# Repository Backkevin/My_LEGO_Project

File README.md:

# My_LEGO_Project

based on MattzoController Firmware V0.3

 My Lego boards with PCF8574 ,MC23017 ,PCA9685 ,L9110
 
 https://www.pcbway.com/setinvite.aspx?inviteid=295257
 
 -----------------------------------------------------------------
 
 BUS PINOUT from CPU Board to other Boards
+ PIN 1 ---> D0
+ PIN 2 ---> SCL (D1)
+ PIN 3 ---> SDA (D2)
+ PIN 4 ---> D3
+ PIN 5 ---> D4
+ PIN 6 ---> D5
+ PIN 7 ---> D6
+ PIN 8 ---> D7
+ PIN 9 ---> D8
+ PIN 10 --> RX
+ PIN 11 --> TX
+ PIN 12 --> D9
+ PIN 13 --> +5VDC (Bug 3A/5A /\ AC/DC BUG 1A)   Layouts are not ready for the 5A BUG (this bug is bigger, change in the next layout)
+ PIN 14 --> +5VDC (Bug 3A/5A /\ AC/DC BUG 1A)   Layouts are not ready for the 5A BUG (this bug is bigger, change in the next layout)
+ PIN 15 --> GND
+ PIN 16 --> GND

-----------------------------------------------------------------

+ PCF8574 adresse
>
+ MCP23017 adresse
>
+ PCA9685 adresse
>
-----------------------------------------------------------------

+ Conpatible sensors and actors
>
>
>
>
>
>
>
>
-----------------------------------------------------------------
-----------------------------------------------------------------

+ [MattzoController_Sensor_Digital_I2C](https://github.com/Backkevin/My_LEGO_Project/tree/master/MattzoController_Sensor_Digital_I2C)

	+ V2.1
		* Work 90%
		* Partlist KO
		* [INO FILE](https://github.com/Backkevin/My_LEGO_Project/tree/master/MattzoController_Sensor_Digital_I2C/INO/MattzoController_Sensor_Digital_I2C)
		* [GERBER FILES](https://github.com/Backkevin/My_LEGO_Project/tree/master/MattzoController_Sensor_Digital_I2C/GERBER%20FILES)
		* [EAGLE FILES](https://github.com/Backkevin/My_LEGO_Project/tree/master/MattzoController_Sensor_Digital_I2C/EAGLE)
		* [PDF FILES](https://github.com/Backkevin/My_LEGO_Project/tree/master/MattzoController_Sensor_Digital_I2C/PDF)
		
	+ Work in progress !
>+ CPU V3.0
>
>+ INPUT V2.1
>
-----------------------------------------------------------------

+ [MattzoController_Signal_I2C](https://github.com/Backkevin/My_LEGO_Project/tree/master/MattzoController_Signal_I2C)

	+ V2.1
		* Work 100%
		* Partlist KO
		* [INO FILE](https://github.com/Backkevin/My_LEGO_Project/tree/master/MattzoController_Signal_I2C/INO/MattzoController_Signal_I2C)
		* [GERBER FILES](https://github.com/Backkevin/My_LEGO_Project/tree/master/MattzoController_Signal_I2C/GERBER%20FILES)
		* [EAGLE FILES](https://github.com/Backkevin/My_LEGO_Project/tree/master/MattzoController_Signal_I2C/EAGLE)
		* [PDF FILES](https://github.com/Backkevin/My_LEGO_Project/tree/master/MattzoController_Signal_I2C/PDF)
		
>+ CPU V3.0
>
>+ OUTPUT V2.1
>
>+ Tower
>
-----------------------------------------------------------------

+ [MattzoController_Switch_I2C](https://github.com/Backkevin/My_LEGO_Project/tree/master/MattzoController_Switch_I2C)

	+ V2.0
		* Work 90%
		* Partlist KO
		* [INO FILE](https://github.com/Backkevin/My_LEGO_Project/tree/master/MattzoController_Switch_I2C/INO/MattzoController_Switch_I2C)
		* [GERBER FILES](https://github.com/Backkevin/My_LEGO_Project/tree/master/MattzoController_Switch_I2C/GERBER%20FILES)
		* [EAGLE FILES](https://github.com/Backkevin/My_LEGO_Project/tree/master/MattzoController_Switch_I2C/EAGLE)
		* [PDF FILES](https://github.com/Backkevin/My_LEGO_Project/tree/master/MattzoController_Switch_I2C/PDF)
		
	+ Work in progress !
>+ CPU V3.0
>
>+ PWM V2.0
>
-----------------------------------------------------------------

+ [MattzoStationController_I2C](https://github.com/Backkevin/My_LEGO_Project/tree/master/MattzoStationController_I2C)

	+ V2.0
		* Work 90%
		* Partlist KO
		* [INO FILE](https://github.com/Backkevin/My_LEGO_Project/tree/master/MattzoStationController_I2C/INO/MattzoStationController_I2C)
		* [GERBER FILES](https://github.com/Backkevin/My_LEGO_Project/tree/master/MattzoStationController_I2C/GERBER%20FILES)
		* [EAGLE FILES](https://github.com/Backkevin/My_LEGO_Project/tree/master/MattzoStationController_I2C/EAGLE)
		* [PDF FILES](https://github.com/Backkevin/My_LEGO_Project/tree/master/MattzoStationController_I2C/PDF)
		
	+ Work in progress !
>+ CPU V3.0
>
>+ INPUT V2.1
>
>+ OUTPUT V2.1
>
>+ PWM V2.0
>
>+ Tower
>
-----------------------------------------------------------------

-----------------------------------------------------------------

+ [MCP23017 Boards I16](https://github.com/Backkevin/My_LEGO_Project/tree/master/MCP23017%20Boards/I16)

	+ V1.0
		* Work 50%
		* Partlist KO
		* [GERBER FILES](https://github.com/Backkevin/My_LEGO_Project/tree/master/MCP23017%20Boards/I16/GERBER%20FILES)
		* [EAGLE FILES](https://github.com/Backkevin/My_LEGO_Project/tree/master/MCP23017%20Boards/I16/EAGLE)
		* [PDF FILES](https://github.com/Backkevin/My_LEGO_Project/tree/master/MCP23017%20Boards/I16/PDF)
		
	+ Work in progress !
>+ CPU V3.0
>
>+ I16 V1.0
>
-----------------------------------------------------------------

+ [MCP23017 Boards O8](https://github.com/Backkevin/My_LEGO_Project/tree/master/MCP23017%20Boards/O8)

+ !!!!!!!  max I for the MCP23017 125ma  so we need to change the R470 resistors to 1K2 
+ or
+ dont install the control LEDs on the board so you can keep the R470 resistors

	+ V1.0
		* Work 50%
		* Partlist KO
		* [GERBER FILES](https://github.com/Backkevin/My_LEGO_Project/tree/master/MCP23017%20Boards/O8/GERBER%20FILES)
		* [EAGLE FILES](https://github.com/Backkevin/My_LEGO_Project/tree/master/MCP23017%20Boards/O8/EAGLE)
		* [PDF FILES](https://github.com/Backkevin/My_LEGO_Project/tree/master/MCP23017%20Boards/O8/PDF)
		
	+ Work in progress !
>+ CPU V3.0
>
>+ O8 V1.0
>
-----------------------------------------------------------------

+ [MCP23017 Boards I8O4](https://github.com/Backkevin/My_LEGO_Project/tree/master/MCP23017%20Boards/I8O4)

	+ V1.0
		* Work 50%
		* Partlist KO
		* [GERBER FILES](https://github.com/Backkevin/My_LEGO_Project/tree/master/MCP23017%20Boards/I8O4/GERBER%20FILES)
		* [EAGLE FILES](https://github.com/Backkevin/My_LEGO_Project/tree/master/MCP23017%20Boards/I8O4/EAGLE)
		* [PDF FILES](https://github.com/Backkevin/My_LEGO_Project/tree/master/MCP23017%20Boards/I8O4/PDF)
		
	+ Work in progress !
>+ V3.0
>
>+ V1.0
>
-----------------------------------------------------------------

-----------------------------------------------------------------

+ [L9110 Board](https://github.com/Backkevin/My_LEGO_Project/tree/master/L9110%20Board)

	+ V1.0
		* Work 25%
		* Partlist KO
		* [GERBER FILES](https://github.com/Backkevin/My_LEGO_Project/tree/master/L9110%20Board/GERBER%20FILES)
		* [EAGLE FILES](https://github.com/Backkevin/My_LEGO_Project/tree/master/L9110%20Board/EAGLE)
		* [PDF FILES](https://github.com/Backkevin/My_LEGO_Project/tree/master/L9110%20Board/PDF)
		
	+ Work in progress !
>+ CPU V3.0
>
>+ L9110 V1.0
>
-----------------------------------------------------------------

SENSOR BOARDS
 
-----------------------------------------------------------------
Experimental
-----------------------------------------------------------------

+ Sensor_GP1A57HRJ00F_board_V_1_0
>
-----------------------------------------------------------------
Sensor_TCRT5000_board_V_1_0
>
-----------------------------------------------------------------
+ Sensor_board_V_1_0
>
-----------------------------------------------------------------
+ Sensor_board_2_V_1_0
>
-----------------------------------------------------------------
+ Sensor_laser_board_V_1_0
>
-----------------------------------------------------------------

-----------------------------------------------------------------
-----------------------------------------------------------------
>i work on a new software based on MattzoController Firmware V0.41

+ [FULL BRIDGE](https://github.com/Backkevin/My_LEGO_Project/tree/master/Universal%20Driver/FULL%20BRIDGE)     
	* --> for 2 x L9110 Board + 2 x I8O4 Board  
	* --> 4 motors, 8 signals, 24 inputs
	* --> AUTO MODE
	* --> later           
+ [FULL CROSSING](https://github.com/Backkevin/My_LEGO_Project/tree/master/Universal%20Driver/FULL%20CROSSING)  
	* --> for PCA9685 Board + 2 x I8O4 Board + 2 x O8 Board                             
	* --> 32 PWMs, 24 signals, 16 inputs 
	* --> AUTO MODE
	* --> later
+ [FULL ELEVATOR](https://github.com/Backkevin/My_LEGO_Project/tree/master/Universal%20Driver/FULL%20ELEVATOR)
	* --> for 2 x L9110 Board + 2 x I8O4 Board + O8 Board + PCA9685 Board      
	* --> 4 motors, 12 signals, 24 inputs, 32 PWMs
	* --> AUTO MODE
	* --> later
+ [FULL SWITCH](https://github.com/Backkevin/My_LEGO_Project/tree/master/Universal%20Driver/FULL%20SWITCH)   
	* --> for PCA9685 Board + 2 x I8O4 Board + 2 x O8 Board                   
	* --> 32 PWMs, 24 signals, 16 inputs 
	* --> AUTO MODE
	* --> later

+ [ONLY INPUT](https://github.com/Backkevin/My_LEGO_Project/tree/master/Universal%20Driver/ONLY%20INPUT)     
	* --> written for PCF8574 or/and MCP23017                       
	* --> you can use both chips at same time (64+128 inputs) 
	* --> but not tested
+ [ONLY SIGNALS](https://github.com/Backkevin/My_LEGO_Project/tree/master/Universal%20Driver/ONLY%20SIGNAL)   
	* --> written for PCF8574 or/and MCP23017           
	* --> you can use both chips at same time (64+128 outputs) 
	* --> but not tested
+ [ONLY SWITCH](https://github.com/Backkevin/My_LEGO_Project/tree/master/Universal%20Driver/ONLY%20SWITCH)    
	* --> written for PCA9685
	* --> but not tested
+ [ONLY BOOM](https://github.com/Backkevin/My_LEGO_Project/tree/master/Universal%20Driver/ONLY%20BOOM)
	* --> written for PCA9685
	* --> but not tested

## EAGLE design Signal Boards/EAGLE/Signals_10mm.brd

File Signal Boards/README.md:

SIGNAL BOARDS
 
-----------------------------------------------------------------

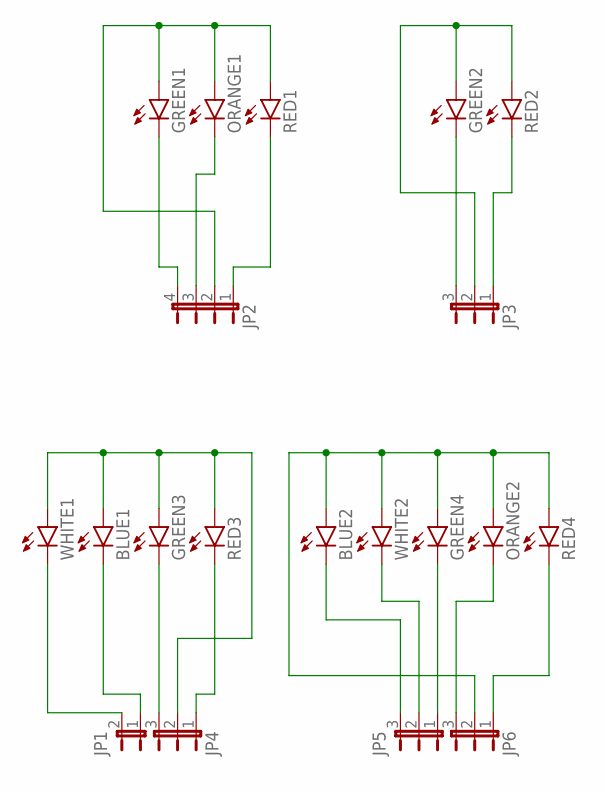
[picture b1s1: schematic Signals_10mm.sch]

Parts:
BLUE1, BLUE2: LED10MM
GREEN1, GREEN2, GREEN3, GREEN4: LED10MM
JP1: JP1E; JP1
JP2: JP4E; JP4
JP3, JP4, JP5, JP6: JP2E; JP2
ORANGE1, ORANGE2: LED10MM
RED1, RED2, RED3, RED4: LED10MM
WHITE1, WHITE2: LED10MM

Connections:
unnamed: GREEN1.A, JP2.2, ORANGE1.A, RED1.A
unnamed: JP2.3, ORANGE1.K (C)
unnamed: JP2.1, RED1.K (C)
unnamed: JP1.2, WHITE1.K (C)
unnamed: GREEN1.K (C), JP2.4
unnamed: GREEN2.A, JP3.2, RED2.A
unnamed: BLUE1.K (C), JP1.1
unnamed: GREEN2.K (C), JP3.3
unnamed: JP3.1, RED2.K (C)
unnamed: GREEN3.K (C), JP4.3
unnamed: JP4.1, RED3.K (C)
unnamed: BLUE1.A, GREEN3.A, JP4.2, RED3.A, WHITE1.A
unnamed: JP6.1, RED4.K (C)
unnamed: JP6.3, ORANGE2.K (C)
unnamed: GREEN4.K (C), JP5.1
unnamed: JP5.2, WHITE2.K (C)
unnamed: BLUE2.K (C), JP5.3
unnamed: BLUE2.A, GREEN4.A, JP6.2, ORANGE2.A, RED4.A, WHITE2.A

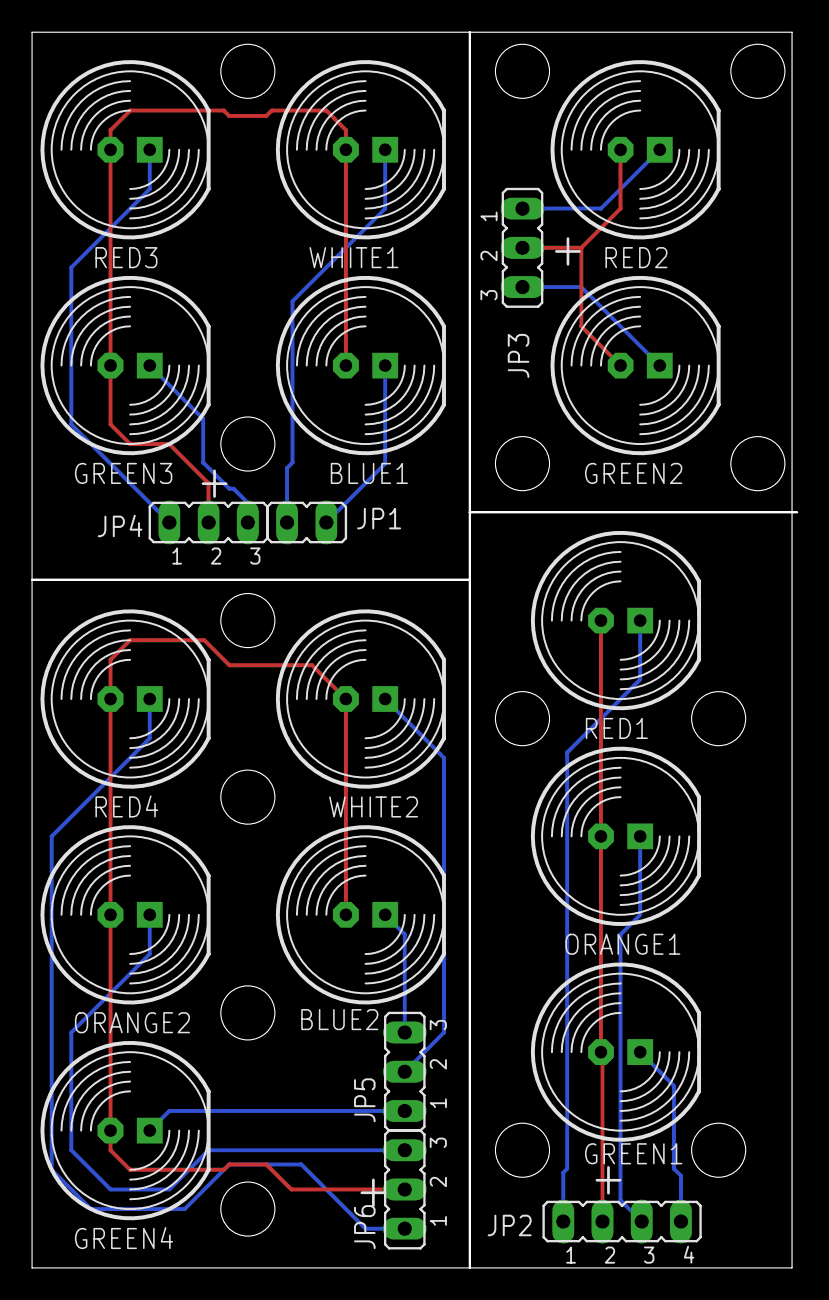
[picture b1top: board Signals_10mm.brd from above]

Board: 2 copper layers, 49.2 x 80.0 mm, 20 parts (0 on the bottom side), 18 nets.

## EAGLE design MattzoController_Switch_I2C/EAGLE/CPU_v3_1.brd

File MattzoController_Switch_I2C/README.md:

# MattzoController_Switch_I2C

-----------------------------------------------------------------

+ MattzoController_Switch_I2C
	+ V2.0
		* Work 90%
		* Partlist not OK
	+ Work in progress !

-----------------------------------------------------------------

-----------------------------------------------------------------

### Partslist Switch
                    
  Part Name   |      PIC      |   Part Info            | Part Quantity |   Part Link 
------------- | ------------- | ---------------------- | ------------- | -------------

-----------------------------------------------------------------

### Partslist CPU
                    
  Part Name   |      PIC      |   Part Info            | Part Quantity |   Part Link 
------------- | ------------- | ---------------------- | ------------- | -------------

-----------------------------------------------------------------

 BUS PINOUT from CPU Board to other Boards
+ PIN 1 ---> D0
+ PIN 2 ---> SCL (D1)
+ PIN 3 ---> SDA (D2)
+ PIN 4 ---> D3
+ PIN 5 ---> D4
+ PIN 6 ---> D5
+ PIN 7 ---> D6
+ PIN 8 ---> D7
+ PIN 9 ---> D8
+ PIN 10 --> RX
+ PIN 11 --> TX
+ PIN 12 --> D9
+ PIN 13 --> +5VDC (Bug 3A/5A /\ AC/DC BUG 1A)
+ PIN 14 --> +5VDC
+ PIN 15 --> GND
+ PIN 16 --> GND

-----------------------------------------------------------------

+ PCF8574 adresse
>
+ PCA9685 adresse
>
+ PINOUT
>
+ OUTPUT AKTORs
>

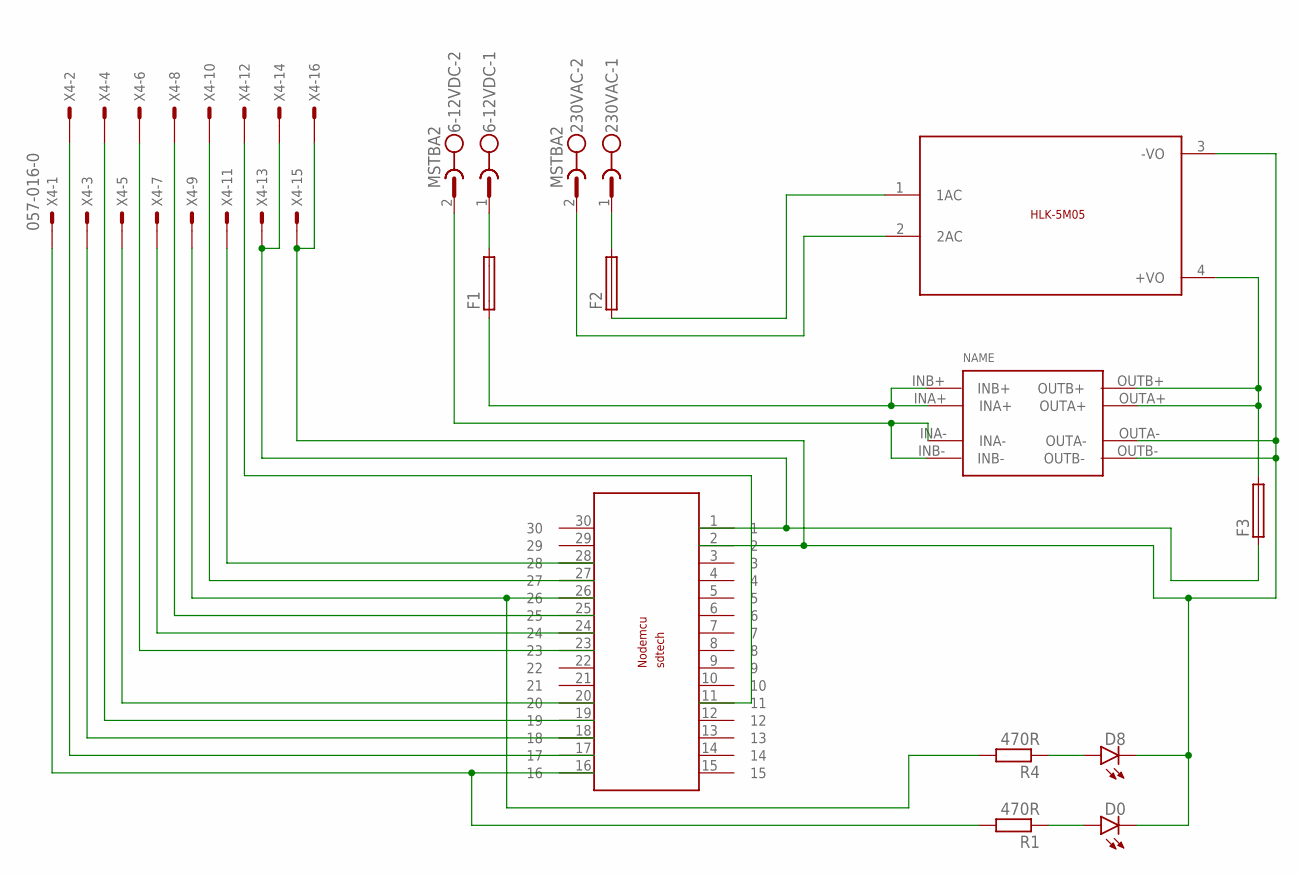
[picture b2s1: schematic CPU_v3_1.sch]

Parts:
6-12VDC, 230VAC: MSTBA2
D0, D8: LED3MM
F1, F2, F3: SH22,5A
R1, R4: 470R; 0309/10
U$1: NODEMCUESP8266
U$2: CP8-ADJ-B
U$3: 5VDC/5W; HLK-5M05
X4: 057-016-0

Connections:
+5VDC: F3.1, U$1.1, X4.13, X4.14
D0: R1.2, U$1.16, X4.1
D8: R4.2, U$1.26, X4.9
D9: U$1.11, X4.12
GND: D0.K (C), D8.K (C), U$1.2, U$2.OUTA-, U$2.OUTB-, U$3.3 (-VO), X4.15, X4.16
unnamed: D8.A, R4.1
unnamed: U$1.19, X4.4
unnamed: D0.A, R1.1
unnamed: 230VAC.1, F2.2
unnamed: F2.1, U$3.1 (1AC)
unnamed: 230VAC.2, U$3.2 (2AC)
unnamed: 6-12VDC.1, F1.2
unnamed: F1.1, U$2.INA+, U$2.INB+
unnamed: 6-12VDC.2, U$2.INA-, U$2.INB-
unnamed: U$1.20, X4.5
unnamed: U$1.23, X4.6
unnamed: U$1.24, X4.7
unnamed: U$1.25, X4.8
unnamed: F3.2, U$2.OUTA+, U$2.OUTB+, U$3.4 (+VO)
RX: U$1.27, X4.10
SCL: U$1.17, X4.2
SDA: U$1.18, X4.3
TX: U$1.28, X4.11

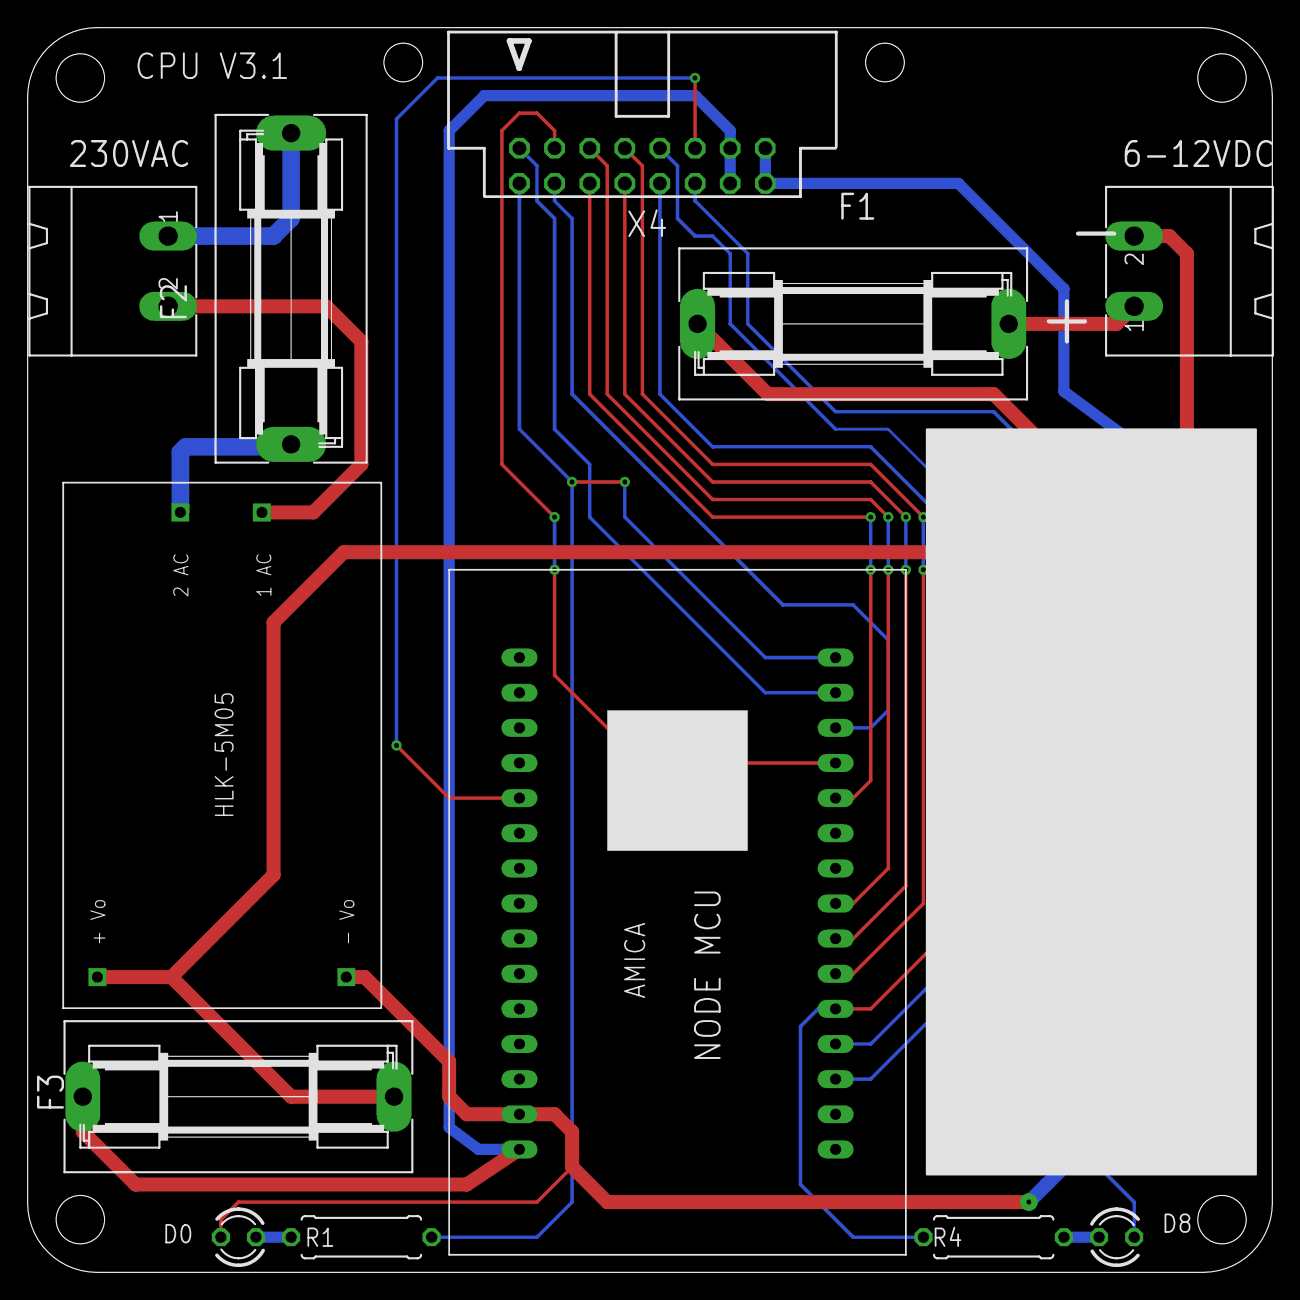
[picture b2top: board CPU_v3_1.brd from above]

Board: 2 copper layers, 90.0 x 90.0 mm, 13 parts (0 on the bottom side), 23 nets.

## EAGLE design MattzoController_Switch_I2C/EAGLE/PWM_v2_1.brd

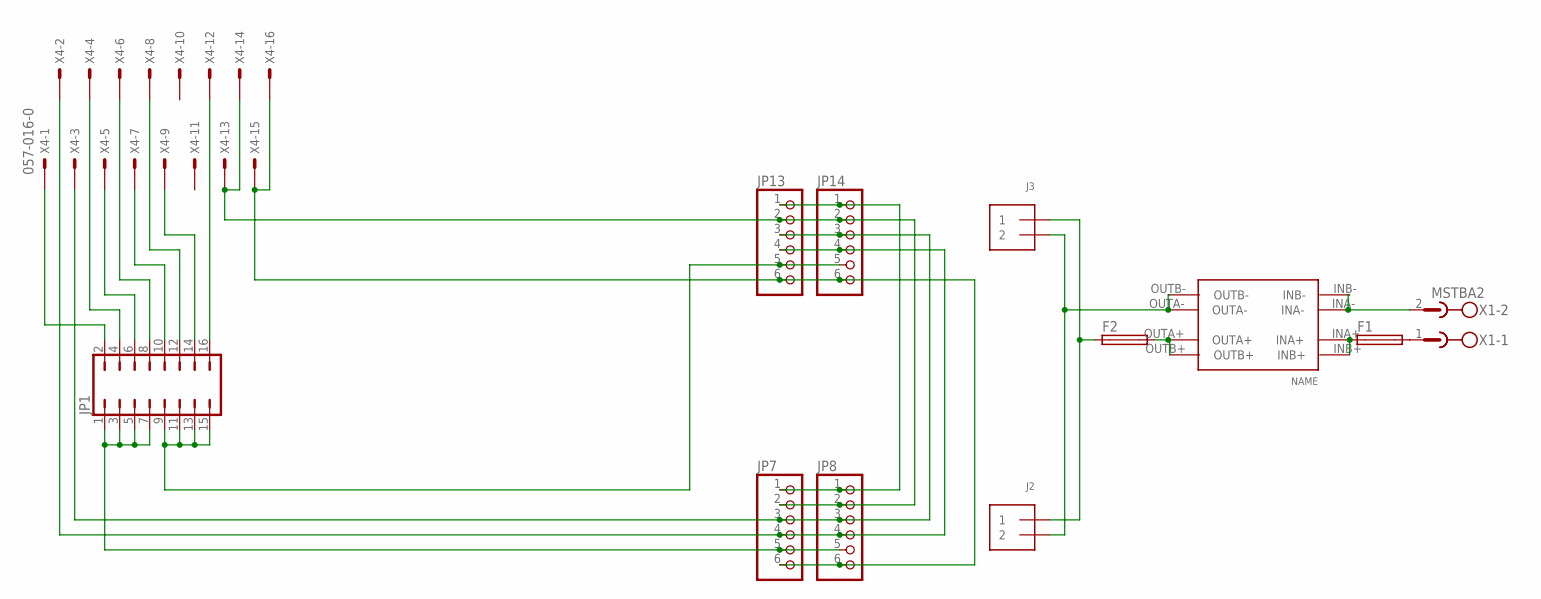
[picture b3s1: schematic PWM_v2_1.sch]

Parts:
F1, F2: SH25
J2, J3: TERMBLOCK_1X2; TERMBLOCK_1X2-3.5MM
JP1: JP8Q
JP7, JP8, JP13, JP14: PINHD-1X6CB; 1X06-CLEANBIG
U$2: CP8-ADJ-B
X1: MSTBA2
X4: 057-016-0

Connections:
unnamed: J2.2, J3.2, U$2.OUTA-, U$2.OUTB-
unnamed: F2.1, J2.1, J3.1
unnamed: JP7.4, JP8.4, JP13.4, JP14.4, X4.2
unnamed: JP1.2, X4.1
unnamed: JP7.6, JP8.6, JP13.6, JP14.6, X4.15, X4.16
unnamed: JP7.1, JP8.1, JP13.1, JP14.1
unnamed: JP7.2, JP8.2, JP13.2, JP14.2, X4.13, X4.14
unnamed: U$2.INA-, U$2.INB-, X1.2
unnamed: F1.1, U$2.INA+, U$2.INB+
unnamed: F1.2, X1.1
unnamed: JP7.3, JP8.3, JP13.3, JP14.3, X4.3
unnamed: F2.2, U$2.OUTA+, U$2.OUTB+
unnamed: JP1.4, X4.4
unnamed: JP1.1, JP1.3, JP1.5, JP1.7, JP7.5, JP8.5
unnamed: JP1.9, JP1.11, JP1.13, JP1.15, JP13.5, JP14.5
unnamed: JP1.6, X4.5
unnamed: JP1.8, X4.6
unnamed: JP1.10, X4.7
unnamed: JP1.12, X4.8
unnamed: JP1.16, X4.12
unnamed: JP1.14, X4.9

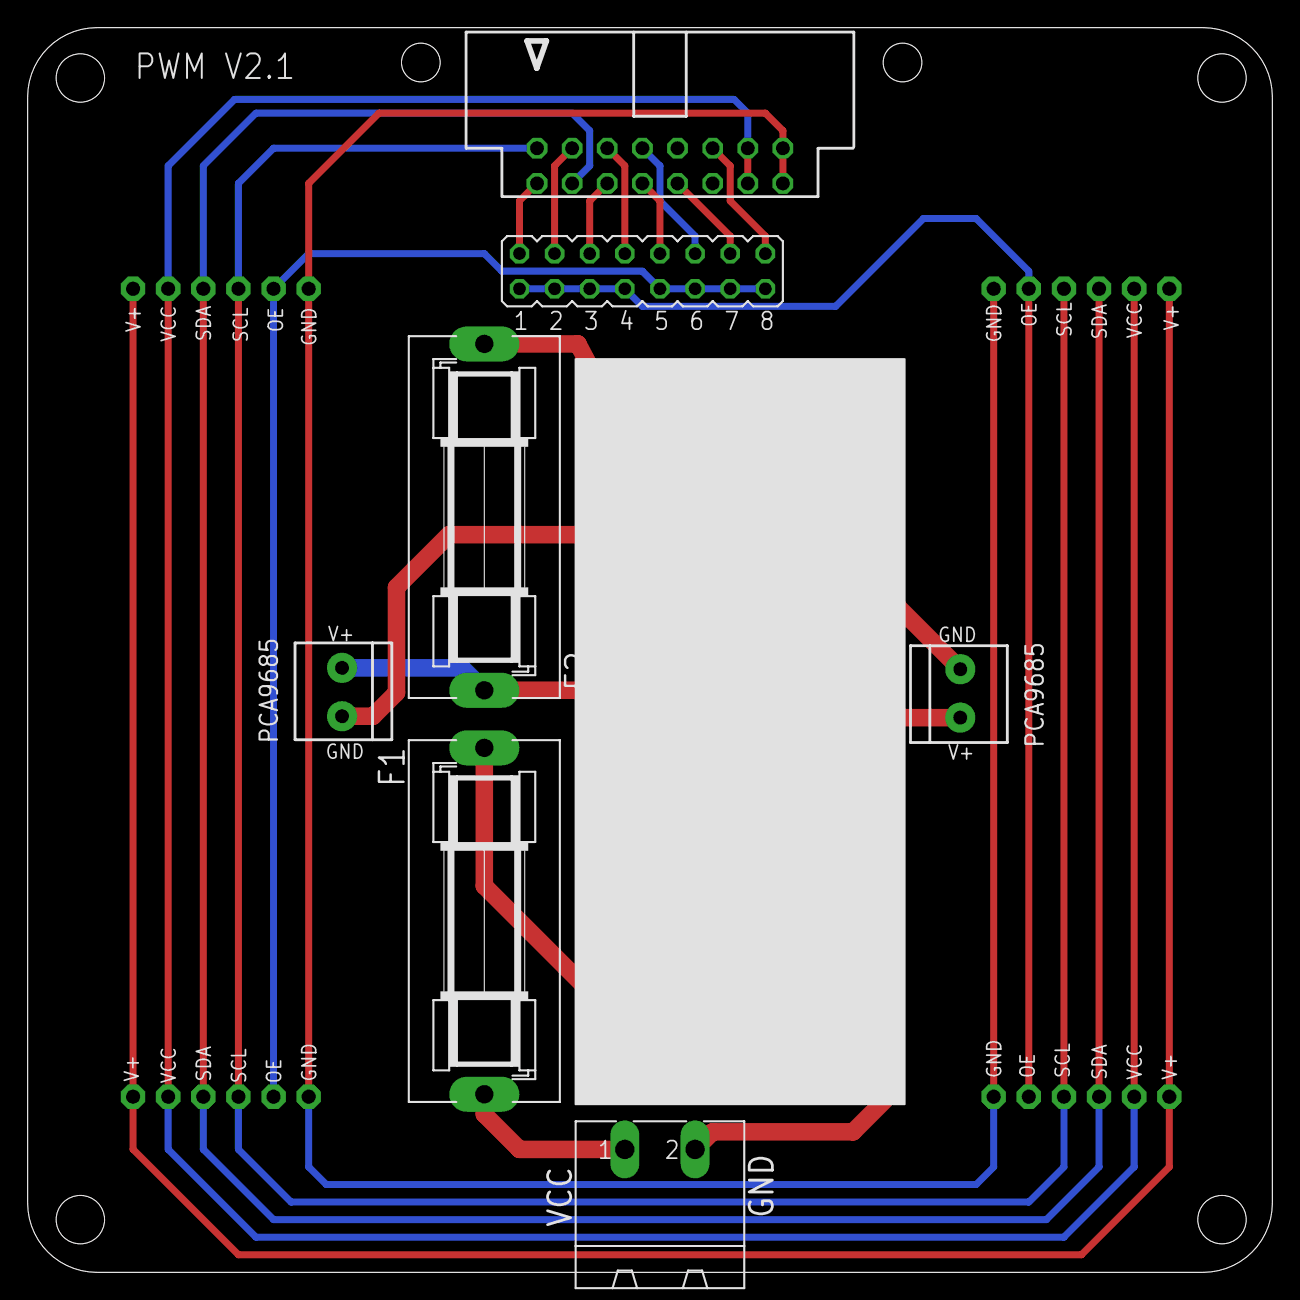
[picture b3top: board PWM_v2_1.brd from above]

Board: 2 copper layers, 90.0 x 90.0 mm, 12 parts (0 on the bottom side), 21 nets.

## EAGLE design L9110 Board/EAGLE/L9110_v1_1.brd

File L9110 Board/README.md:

+ [L9110 Board](https://github.com/Backkevin/My_LEGO_Project/tree/master/L9110%20Board)
+ 8 Inputs and 4 motor Outputs with extra power in

	+ V1.0
		* Work 25%
		* Partlist KO
		* [GERBER FILES](https://github.com/Backkevin/My_LEGO_Project/tree/master/L9110%20Board/GERBER%20FILES)
		* [EAGLE FILES](https://github.com/Backkevin/My_LEGO_Project/tree/master/L9110%20Board/EAGLE)
		* [PDF FILES](https://github.com/Backkevin/My_LEGO_Project/tree/master/L9110%20Board/PDF)
		
	+ Work in progress !
>+ V3.0
>
>+ V1.0
>

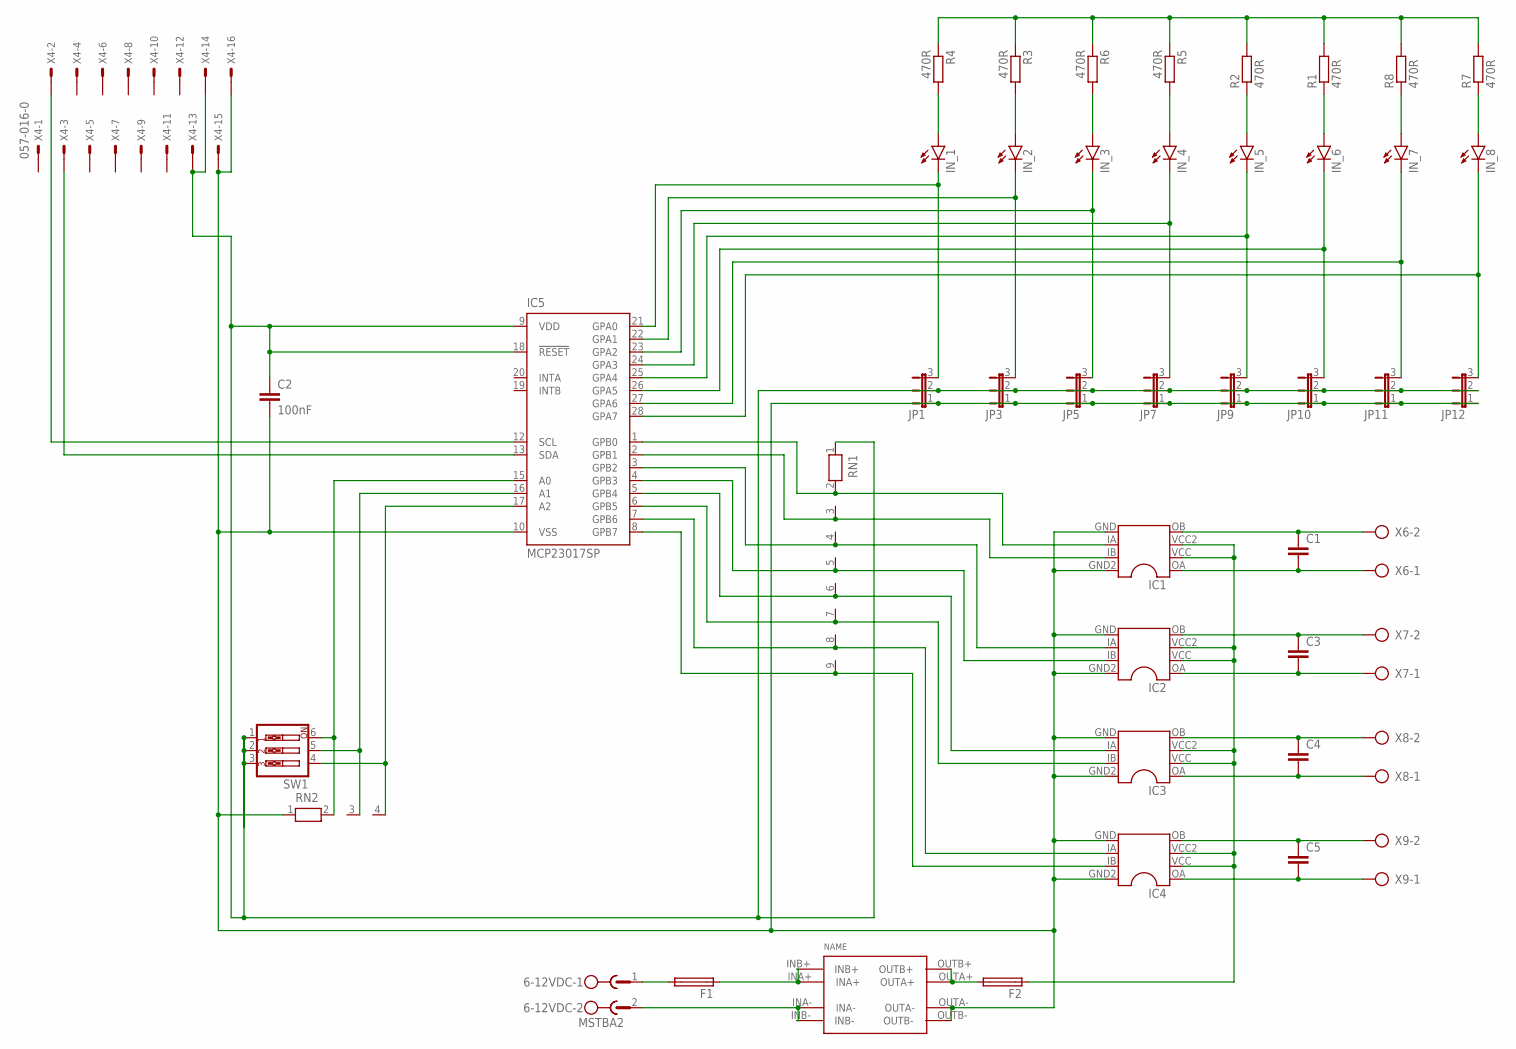
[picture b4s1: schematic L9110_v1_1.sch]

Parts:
6-12VDC: MSTBA2
C1, C3, C4, C5: C-EU025-024X044; C025-024X044
C2: 100nF; C025-024X044
F1, F2: SH22,5A
IC1, IC2, IC3, IC4: L9110
IC5: MCP23017SP; DIL28-3
IN_1, IN_2, IN_3, IN_4, IN_5, IN_6, IN_7, IN_8: LED3MM
JP1, JP3, JP5, JP7, JP9, JP10, JP11, JP12: JP2E; JP2
R1, R2, R3, R4, R5, R6, R7, R8: 470R; 0309/10
RN1: RN08; RN-9
RN2: RN03; RN-3
SW1: SW_DIP-3; EDG-03
U$2: CP8-ADJ-B
X4: 057-016-0
X6, X7, X8, X9: AK300/2

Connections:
GND2: C2.2, IC1.GND (5), IC1.GND2 (8), IC2.GND (5), IC2.GND2 (8), IC3.GND (5), IC3.GND2 (8), IC4.GND (5), IC4.GND2 (8), IC5.10 (VSS), JP1.1, JP3.1, JP5.1, JP7.1, JP9.1, JP10.1, JP11.1, JP12.1, RN2.1, U$2.OUTA-, U$2.OUTB-, X4.15, X4.16
unnamed: IC1.IA (6), IC5.1 (GPB0), RN1.2
unnamed: IC5.22 (GPA1), IN_2.K (C), JP3.3
unnamed: IC1.IB (7), IC5.2 (GPB1), RN1.3
unnamed: IC5.24 (GPA3), IN_4.K (C), JP7.3
unnamed: IC2.IA (6), IC5.3 (GPB2), RN1.4
unnamed: IC5.17 (A2), RN2.4, SW1.4
unnamed: IC5.26 (GPA5), IN_6.K (C), JP10.3
unnamed: IC2.IB (7), IC5.4 (GPB3), RN1.5
unnamed: IC5.28 (GPA7), IN_8.K (C), JP12.3
unnamed: IN_8.A, R7.1
unnamed: IN_7.A, R8.1
unnamed: IC3.IA (6), IC5.5 (GPB4), RN1.6
unnamed: IN_6.A, R1.1
unnamed: IC3.IB (7), IC5.6 (GPB5), RN1.7
unnamed: IC4.IA (6), IC5.7 (GPB6), RN1.8
unnamed: IC4.IB (7), IC5.8 (GPB7), RN1.9
unnamed: C1.1, IC1.OB (4), X6.2
unnamed: F2.1, IC1.VCC (2), IC1.VCC2 (3), IC2.VCC (2), IC2.VCC2 (3), IC3.VCC (2), IC3.VCC2 (3), IC4.VCC (2), IC4.VCC2 (3)
unnamed: C1.2, IC1.OA (1), X6.1
unnamed: C3.1, IC2.OB (4), X7.2
unnamed: IC5.21 (GPA0), IN_1.K (C), JP1.3
unnamed: C3.2, IC2.OA (1), X7.1
unnamed: IC5.23 (GPA2), IN_3.K (C), JP5.3
unnamed: C4.1, IC3.OB (4), X8.2
unnamed: IC5.25 (GPA4), IN_5.K (C), JP9.3
unnamed: C4.2, IC3.OA (1), X8.1
unnamed: IC5.27 (GPA6), IN_7.K (C), JP11.3
unnamed: C5.1, IC4.OB (4), X9.2
unnamed: IN_5.A, R2.1
unnamed: IN_4.A, R5.2
unnamed: IN_3.A, R6.2
unnamed: IN_2.A, R3.2
unnamed: IN_1.A, R4.2
unnamed: C5.2, IC4.OA (1), X9.1
unnamed: IC5.16 (A1), RN2.3, SW1.5
unnamed: 6-12VDC.1, F1.2
unnamed: F1.1, U$2.INA+, U$2.INB+
unnamed: 6-12VDC.2, U$2.INA-, U$2.INB-
unnamed: F2.2, U$2.OUTA+, U$2.OUTB+
unnamed: IC5.12 (SCL), X4.2
unnamed: IC5.13 (SDA), X4.3
unnamed: IC5.15 (A0), RN2.2, SW1.6
VCC5.1: C2.1, IC5.9 (VDD), IC5.18 (!RESET), JP1.2, JP3.2, JP5.2, JP7.2, JP9.2, JP10.2, JP11.2, JP12.2, RN1.1, SW1.1, SW1.2, SW1.3, X4.13, X4.14
VCC5.2: R1.2, R2.2, R3.1, R4.1, R5.1, R6.1, R7.2, R8.2

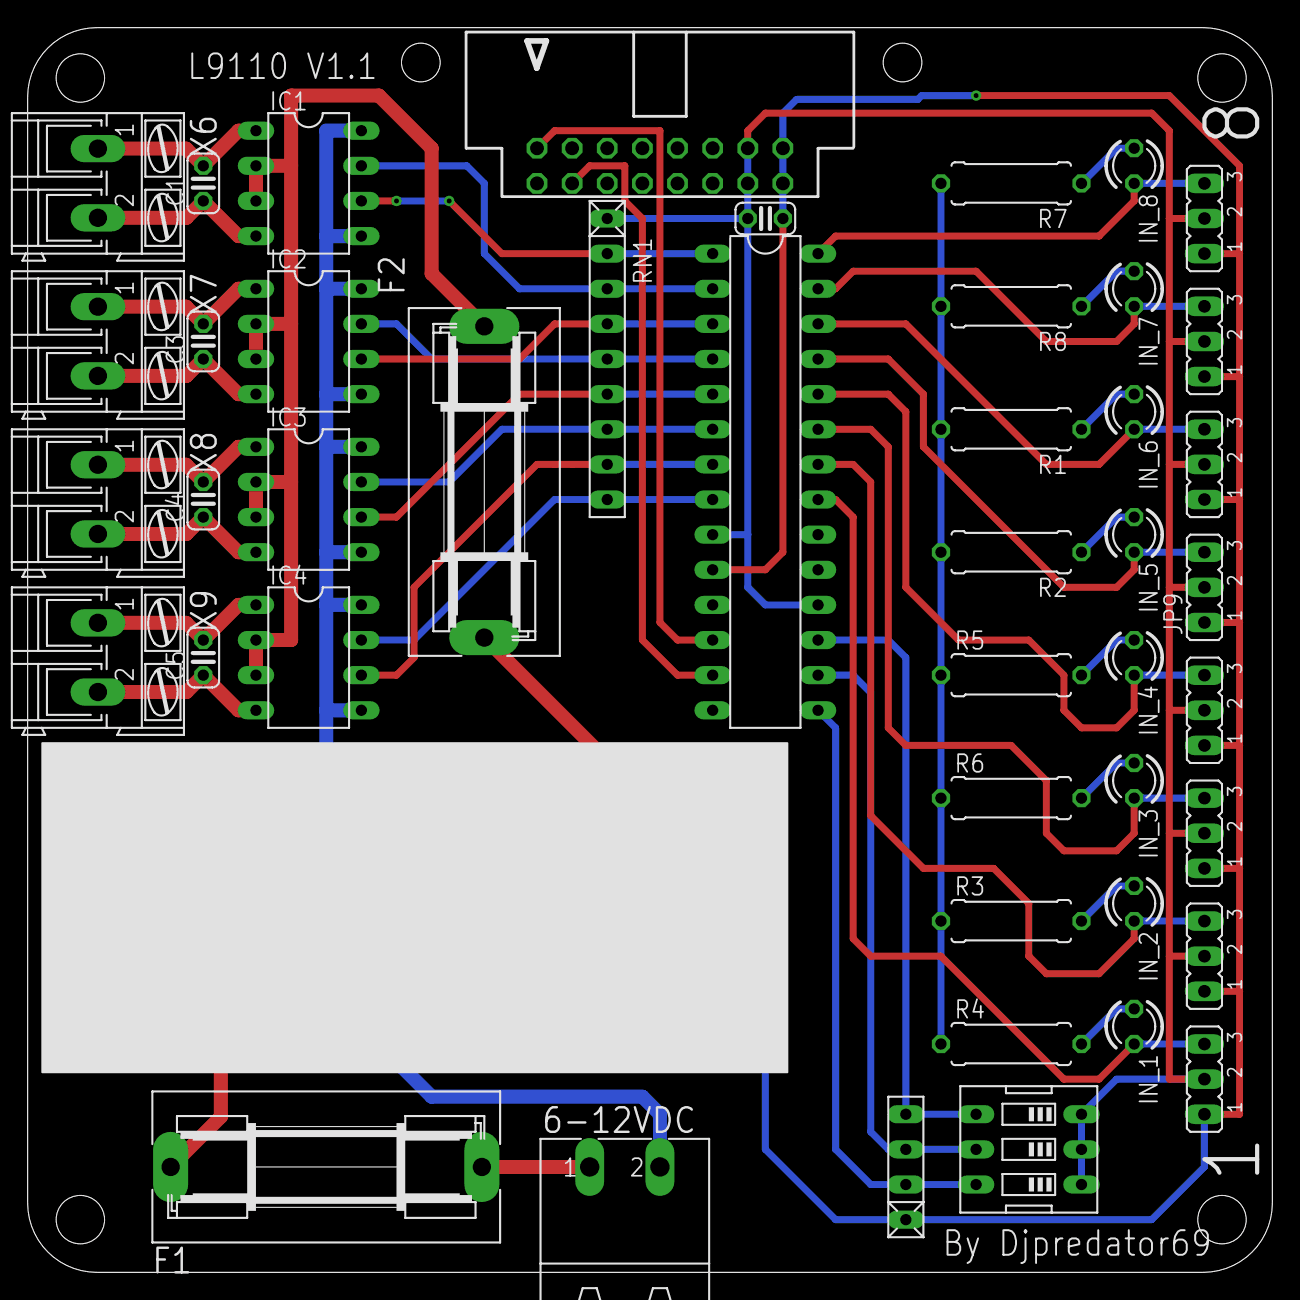
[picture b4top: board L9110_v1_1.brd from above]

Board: 2 copper layers, 90.0 x 90.0 mm, 46 parts (0 on the bottom side), 45 nets.

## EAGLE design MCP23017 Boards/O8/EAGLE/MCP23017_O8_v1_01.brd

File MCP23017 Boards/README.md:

# MCP23017 Boards
+ [I16](https://github.com/Backkevin/My_LEGO_Project/tree/master/MCP23017%20Boards/I16)
	+ V1.0
		* Work 50%
		* Partlist not OK
		* [GERBER FILES](https://github.com/Backkevin/My_LEGO_Project/tree/master/MCP23017%20Boards/I16/GERBER%20FILES)
		* [EAGLE FILES](https://github.com/Backkevin/My_LEGO_Project/tree/master/MCP23017%20Boards/I16/EAGLE)
		* [PDF FILES](https://github.com/Backkevin/My_LEGO_Project/tree/master/MCP23017%20Boards/I16/PDF)
	+ Work in progress !

+ [I8O4](https://github.com/Backkevin/My_LEGO_Project/tree/master/MCP23017%20Boards/I8O4)
	+ V1.0
		* Work 50%
		* Partlist not OK
		* [GERBER FILES](https://github.com/Backkevin/My_LEGO_Project/tree/master/MCP23017%20Boards/I8O4/GERBER%20FILES)
		* [EAGLE FILES](https://github.com/Backkevin/My_LEGO_Project/tree/master/MCP23017%20Boards/I8O4/EAGLE)
		* [PDF FILES](https://github.com/Backkevin/My_LEGO_Project/tree/master/MCP23017%20Boards/I8O4/PDF)
	+ Work in progress !

+ [O8](https://github.com/Backkevin/My_LEGO_Project/tree/master/MCP23017%20Boards/O8)
	
+ !!!!!!!  max I for the MCP23017 125ma  so we need to change the R470 resistors to 1K2 
+ or
+ dont install the control LEDs on the board so you can keep the R470 resistors

	+ V1.0
		* Work 50%
		* Partlist not OK
		* [GERBER FILES](https://github.com/Backkevin/My_LEGO_Project/tree/master/MCP23017%20Boards/O8/GERBER%20FILES)
		* [EAGLE FILES](https://github.com/Backkevin/My_LEGO_Project/tree/master/MCP23017%20Boards/O8/EAGLE)
		* [PDF FILES](https://github.com/Backkevin/My_LEGO_Project/tree/master/MCP23017%20Boards/O8/PDF)
	+ Work in progress !

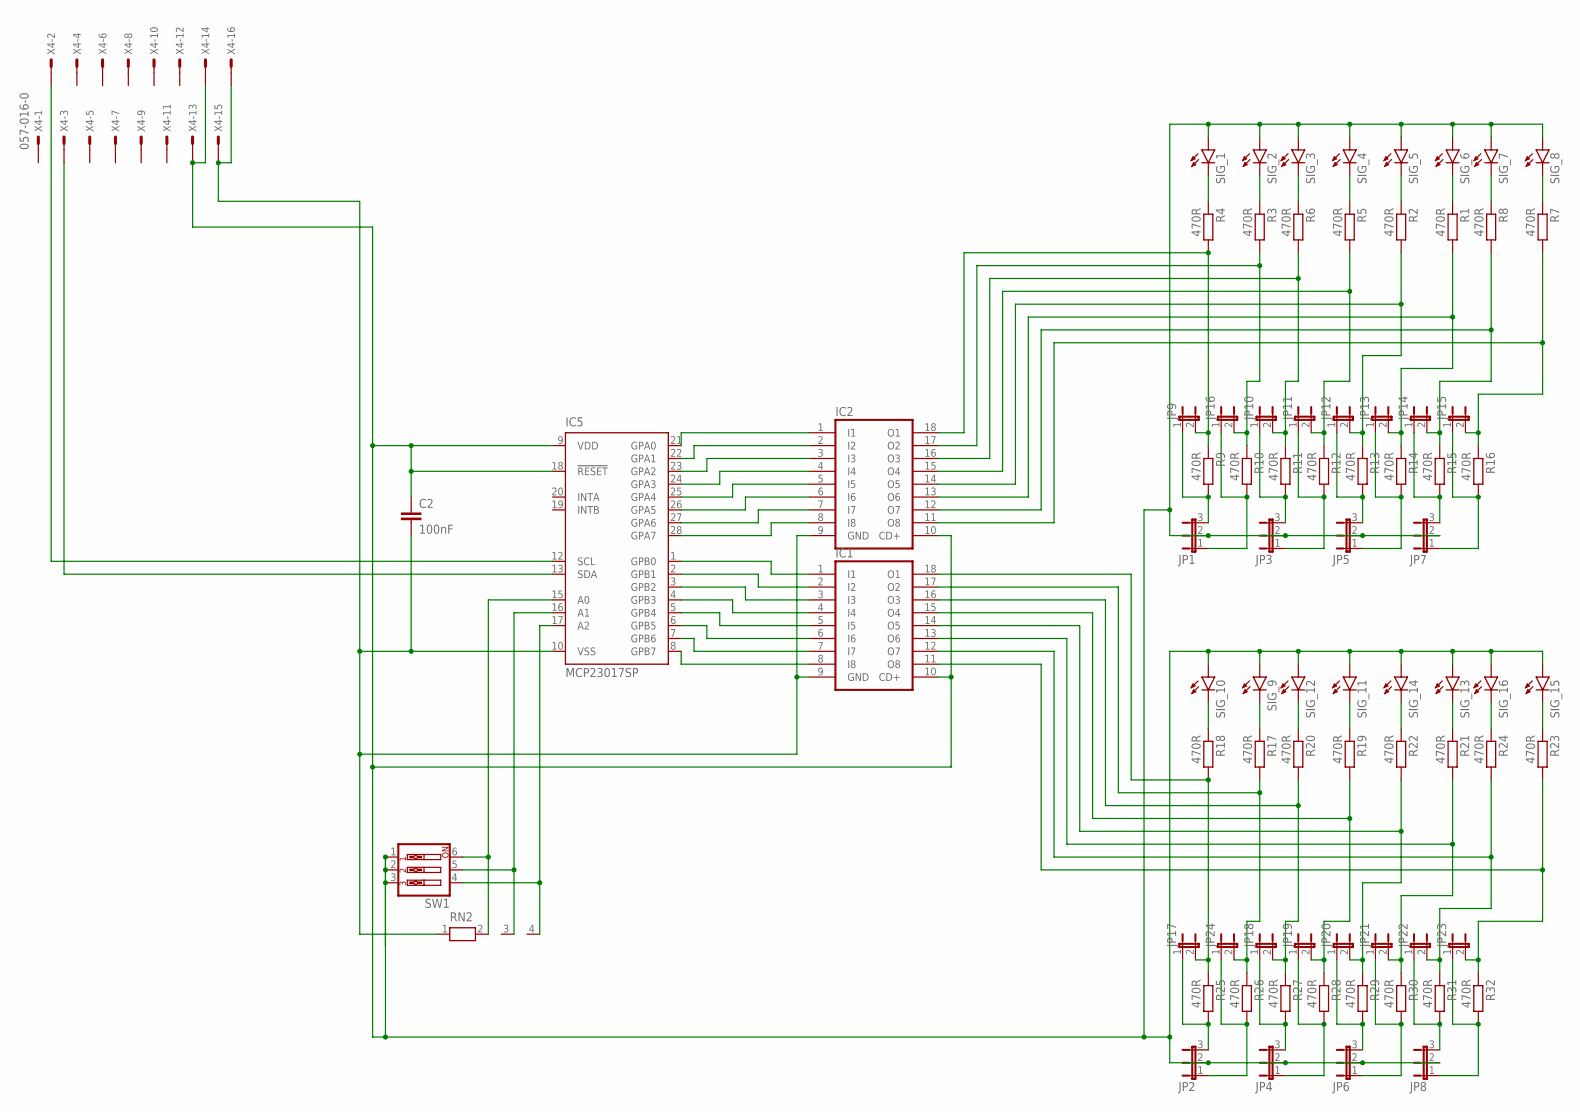
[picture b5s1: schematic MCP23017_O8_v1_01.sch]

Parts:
C2: 100nF; C025-024X044
IC1, IC2: ULN2803A; DIL18
IC5: MCP23017SP; DIL28-3
JP1, JP2, JP3, JP4, JP5, JP6, JP7, JP8: JP2E; JP2
JP9, JP10, JP11, JP12, JP13, JP14, JP15, JP16, JP17, JP18, JP19, JP20, JP21, JP22, JP23, JP24: JP1E; JP1
R1, R2, R3, R4, R5, R6, R7, R8, R9, R10, R11, R12, R13, R14, R15, R16, R17, R18, R19, R20, R21, R22, R23, R24, R25, R26, R27, R28, R29, R30, R31, R32: 470R; 0309/10
RN2: RN03; RN-3
SIG_1, SIG_2, SIG_3, SIG_4, SIG_5, SIG_6, SIG_7, SIG_8, SIG_9, SIG_10, SIG_11, SIG_12, SIG_13, SIG_14, SIG_15, SIG_16: LED3MM
SW1: SW_DIP-3; EDG-03
X4: 057-016-0

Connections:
GND2: C2.2, IC1.9 (GND), IC2.9 (GND), IC5.10 (VSS), RN2.1, X4.15, X4.16
unnamed: JP1.3, JP9.1, R9.2
unnamed: IC2.18 (O1), JP9.2, R4.2, R9.1
unnamed: R2.1, SIG_5.K (C)
unnamed: R1.1, SIG_6.K (C)
unnamed: IC2.1 (I1), IC5.21 (GPA0)
unnamed: IC5.17 (A2), RN2.4, SW1.4
unnamed: R8.1, SIG_7.K (C)
unnamed: R7.1, SIG_8.K (C)
unnamed: JP1.1, JP16.1, R10.2
unnamed: JP3.3, JP10.1, R11.2
unnamed: JP3.1, JP11.1, R12.2
unnamed: IC2.16 (O3), JP10.2, R6.2, R11.1
unnamed: JP5.3, JP12.1, R13.2
unnamed: IC2.14 (O5), JP12.2, R2.2, R13.1
unnamed: IC1.17 (O2), JP24.2, R17.2, R26.1
unnamed: IC1.15 (O4), JP19.2, R19.2, R28.1
unnamed: IC1.14 (O5), JP20.2, R22.2, R29.1
unnamed: IC1.18 (O1), JP17.2, R18.2, R25.1
unnamed: IC2.17 (O2), JP16.2, R3.2, R10.1
unnamed: IC2.15 (O4), JP11.2, R5.2, R12.1
unnamed: IC2.2 (I2), IC5.22 (GPA1)
unnamed: IC2.3 (I3), IC5.23 (GPA2)
unnamed: IC2.4 (I4), IC5.24 (GPA3)
unnamed: JP5.1, JP13.1, R14.2
unnamed: IC2.5 (I5), IC5.25 (GPA4)
unnamed: JP7.3, JP14.1, R15.2
unnamed: JP7.1, JP15.1, R16.2
unnamed: IC2.6 (I6), IC5.26 (GPA5)
unnamed: IC5.16 (A1), RN2.3, SW1.5
unnamed: R4.1, SIG_1.K (C)
unnamed: R3.1, SIG_2.K (C)
unnamed: IC2.7 (I7), IC5.27 (GPA6)
unnamed: IC2.8 (I8), IC5.28 (GPA7)
unnamed: IC1.1 (I1), IC5.1 (GPB0)
unnamed: IC1.2 (I2), IC5.2 (GPB1)
unnamed: IC1.3 (I3), IC5.3 (GPB2)
unnamed: IC1.4 (I4), IC5.4 (GPB3)
unnamed: IC1.5 (I5), IC5.5 (GPB4)
unnamed: IC1.6 (I6), IC5.6 (GPB5)
unnamed: IC1.7 (I7), IC5.7 (GPB6)
unnamed: IC1.8 (I8), IC5.8 (GPB7)
unnamed: IC1.13 (O6), JP21.2, R21.2, R30.1
unnamed: IC1.16 (O3), JP18.2, R20.2, R27.1
unnamed: IC1.12 (O7), JP22.2, R24.2, R31.1
unnamed: R6.1, SIG_3.K (C)
unnamed: R5.1, SIG_4.K (C)
unnamed: IC1.11 (O8), JP23.2, R23.2, R32.1
unnamed: IC2.13 (O6), JP13.2, R1.2, R14.1
unnamed: IC2.12 (O7), JP14.2, R8.2, R15.1
unnamed: IC2.11 (O8), JP15.2, R7.2, R16.1
unnamed: R18.1, SIG_10.K (C)
unnamed: R17.1, SIG_9.K (C)
unnamed: R20.1, SIG_12.K (C)
unnamed: R19.1, SIG_11.K (C)
unnamed: R22.1, SIG_14.K (C)
unnamed: R21.1, SIG_13.K (C)
unnamed: R24.1, SIG_16.K (C)
unnamed: R23.1, SIG_15.K (C)
unnamed: JP2.3, JP17.1, R25.2
unnamed: JP2.1, JP24.1, R26.2
unnamed: JP4.3, JP18.1, R27.2
unnamed: JP4.1, JP19.1, R28.2
unnamed: JP6.3, JP20.1, R29.2
unnamed: JP6.1, JP21.1, R30.2
unnamed: JP8.3, JP22.1, R31.2
unnamed: JP8.1, JP23.1, R32.2
unnamed: IC5.12 (SCL), X4.2
unnamed: IC5.13 (SDA), X4.3
unnamed: IC5.15 (A0), RN2.2, SW1.6
VCC5.1: C2.1, IC1.10 (CD+), IC2.10 (CD+), IC5.9 (VDD), IC5.18 (!RESET), JP1.2, JP2.2, JP3.2, JP4.2, JP5.2, JP6.2, JP7.2, JP8.2, SIG_1.A, SIG_2.A, SIG_3.A, SIG_4.A, SIG_5.A, SIG_6.A, SIG_7.A, SIG_8.A, SIG_9.A, SIG_10.A, SIG_11.A, SIG_12.A, SIG_13.A, SIG_14.A, SIG_15.A, SIG_16.A, SW1.1, SW1.2, SW1.3, X4.13, X4.14
